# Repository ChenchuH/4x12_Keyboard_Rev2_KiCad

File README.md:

# 4x12_Keyboard_Rev2_KiCad
4x12 Ortholinear Keeb with RP2040

## Bill of Materials

| Reference(s) | Qty | Value | Footprint |
|---|---:|---|---|
| D1–D48 | 48 | 1N4148W | `Diode_SMD:D_SOD-123` |
| ENC1 | 1 | RotaryEncoder | `Rotary_Encoder:RotaryEncoder_Alps_EC12E_Vertical_H20mm` |
| LED1 | 1 | 3V | `LED_SMD:LED_0805_2012Metric_Pad1.15x1.40mm_HandSolder` |
| LED2 | 1 | 2.1 | `LED_SMD:LED_0805_2012Metric_Pad1.15x1.40mm_HandSolder` |
| Q1 | 1 | MMBT3904 | `Package_TO_SOT_SMD:SOT-23` |
| R1 | 1 | 100 | `Resistor_SMD:R_0805_2012Metric` |
| R2 | 1 | 1k | `Resistor_SMD:R_0805_2012Metric` |
| R3 | 1 | 330 | `Resistor_SMD:R_0805_2012Metric` |
| SW1–SW48 | 48 | SW_Push | `Keyboardparts:SW_Cherry_MX_1.00u_PCB_NoSilkScreen` |
| U1 | 1 | XIAO-RP2040-Plus-SMD | `Seeed_XIAO:XIAO-RP2040-Plus-SMD` |

### 5 PCBs cost roughly $60 USD from JLPCB, be sure to get a stencil as well for SMD diodes, 48 will get tedious and difficult even in the 0805 package.

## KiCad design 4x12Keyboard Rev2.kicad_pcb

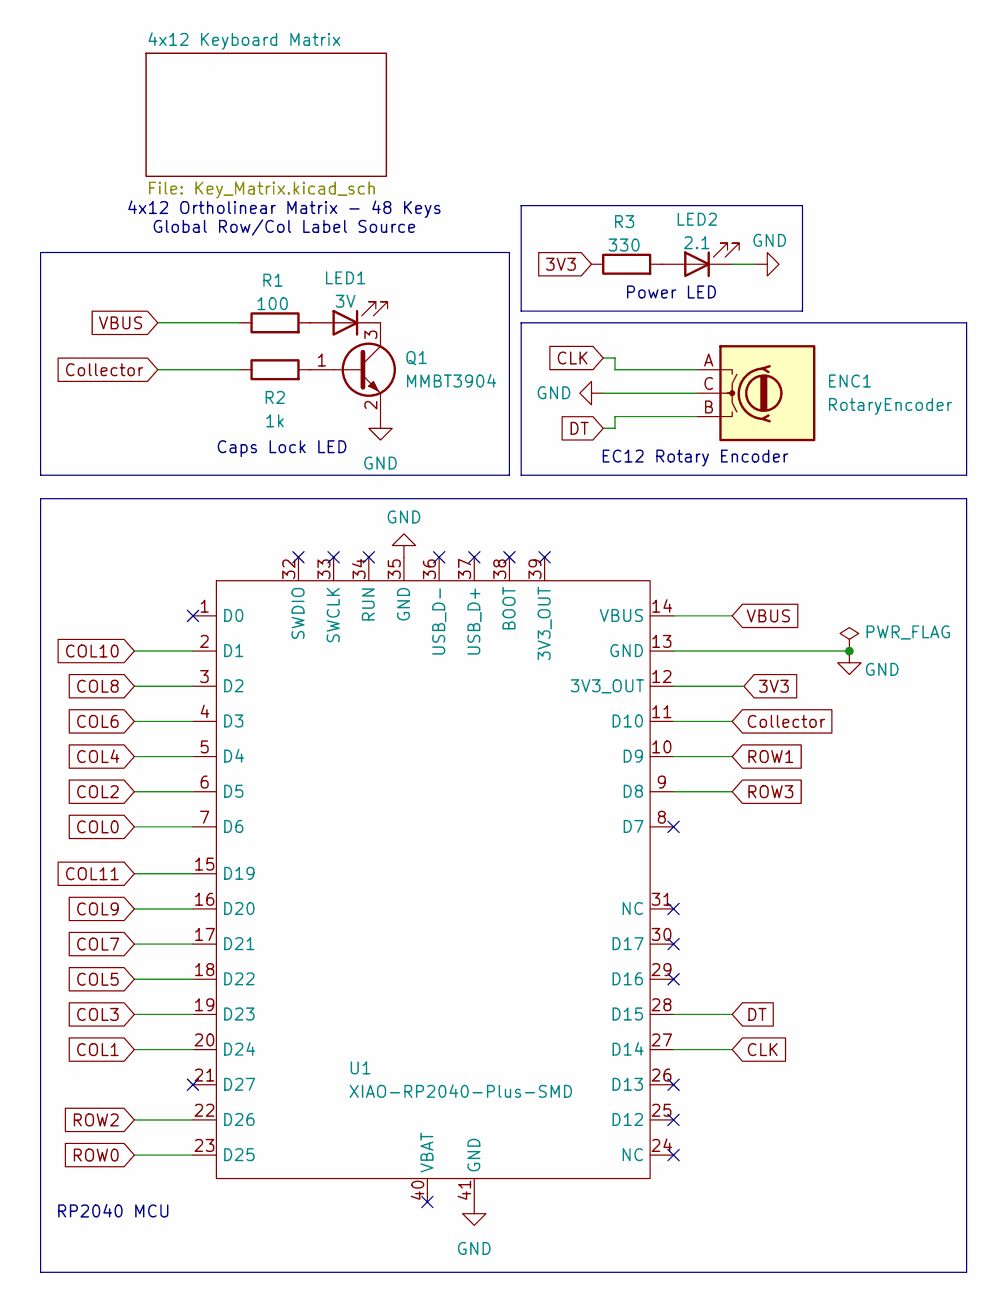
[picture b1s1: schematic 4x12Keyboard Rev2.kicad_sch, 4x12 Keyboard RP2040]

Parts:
ENC1: RotaryEncoder; RotaryEncoder_Alps_EC12E_Vertical_H20mm
LED1: 3V; LED_0805_2012Metric_Pad1.15x1.40mm_HandSolder
LED2: 2.1; LED_0805_2012Metric_Pad1.15x1.40mm_HandSolder
Q1: MMBT3904; SOT-23
R1: 100; R_0805_2012Metric_Pad1.20x1.40mm_HandSolder
R2: 1k; R_0805_2012Metric_Pad1.20x1.40mm_HandSolder
R3: 330; R_0805_2012Metric_Pad1.20x1.40mm_HandSolder
U1: XIAO-RP2040-Plus-SMD

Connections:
3V3: R3.1, U1.12 (3V3_OUT)
CLK: ENC1.A, U1.27 (D14)
COL0: U1.7 (D6); also elsewhere on the board
COL1: U1.20 (D24); also elsewhere on the board
COL2: U1.6 (D5); also elsewhere on the board
COL3: U1.19 (D23); also elsewhere on the board
COL4: U1.5 (D4); also elsewhere on the board
COL5: U1.18 (D22); also elsewhere on the board
COL6: U1.4 (D3); also elsewhere on the board
COL7: U1.17 (D21); also elsewhere on the board
COL8: U1.3 (D2); also elsewhere on the board
COL9: U1.16 (D20); also elsewhere on the board
COL10: U1.2 (D1); also elsewhere on the board
COL11: U1.15 (D19); also elsewhere on the board
Collector: R2.1, U1.11 (D10)
DT: ENC1.B, U1.28 (D15)
GND: ENC1.C, LED2.1 (K), Q1.2 (E), U1.13 (GND), U1.35 (GND), U1.41 (GND)
unnamed: LED1.2 (A), R1.2
unnamed: LED1.1 (K), Q1.3 (C)
unnamed: LED2.2 (A), R3.2
unnamed: Q1.1 (B), R2.2
ROW0: U1.23 (D25); also elsewhere on the board
ROW1: U1.10 (D9); also elsewhere on the board
ROW2: U1.22 (D26); also elsewhere on the board
ROW3: U1.9 (D8); also elsewhere on the board
VBUS: R1.1, U1.14 (VBUS)

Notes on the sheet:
Caps Lock LED
4x12 Ortholinear Matrix - 48 Keys Global Row/Col Label Source
EC12 Rotary Encoder
RP2040 MCU
Power LED

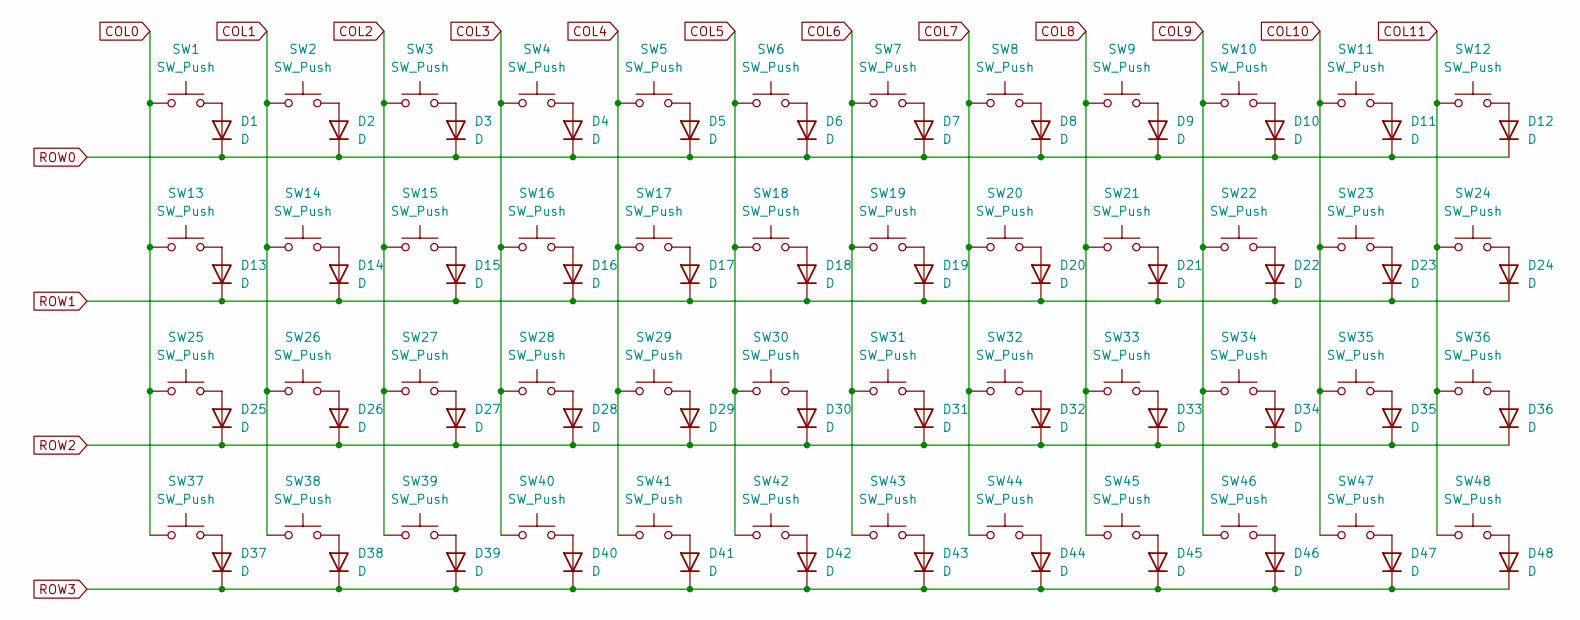
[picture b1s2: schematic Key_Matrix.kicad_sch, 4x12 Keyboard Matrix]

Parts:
D1, D2, D3, D4, D5, D6, D7, D8, D9, D10, D11, D12, D13, D14, D15, D16, D17, D18, D19, D20, D21, D22, D23, D24, D25, D26, D27, D28, D29, D30, D31, D32, D33, D34, D35, D36, D37, D38, D39, D40, D41, D42, D43, D44, D45, D46, D47, D48: D; D_SOD-123
SW1, SW2, SW3, SW4, SW5, SW6, SW7, SW8, SW9, SW10, SW11, SW12, SW13, SW14, SW15, SW16, SW17, SW18, SW19, SW20, SW21, SW22, SW23, SW24, SW25, SW26, SW27, SW28, SW29, SW30, SW31, SW32, SW33, SW34, SW35, SW36, SW37, SW38, SW39, SW40, SW41, SW42, SW43, SW44, SW45, SW46, SW47, SW48: SW_Push; SW_Cherry_MX_1.00u_PCB_NoSilkScreen

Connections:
COL0: SW1.1, SW13.1, SW25.1, SW37.1; also elsewhere on the board
COL1: SW2.1, SW14.1, SW26.1, SW38.1; also elsewhere on the board
COL2: SW3.1, SW15.1, SW27.1, SW39.1; also elsewhere on the board
COL3: SW4.1, SW16.1, SW28.1, SW40.1; also elsewhere on the board
COL4: SW5.1, SW17.1, SW29.1, SW41.1; also elsewhere on the board
COL5: SW6.1, SW18.1, SW30.1, SW42.1; also elsewhere on the board
COL6: SW7.1, SW19.1, SW31.1, SW43.1; also elsewhere on the board
COL7: SW8.1, SW20.1, SW32.1, SW44.1; also elsewhere on the board
COL8: SW9.1, SW21.1, SW33.1, SW45.1; also elsewhere on the board
COL9: SW10.1, SW22.1, SW34.1, SW46.1; also elsewhere on the board
COL10: SW11.1, SW23.1, SW35.1, SW47.1; also elsewhere on the board
COL11: SW12.1, SW24.1, SW36.1, SW48.1; also elsewhere on the board
unnamed: D1.2 (A), SW1.2
unnamed: D2.2 (A), SW2.2
unnamed: D3.2 (A), SW3.2
unnamed: D4.2 (A), SW4.2
unnamed: D5.2 (A), SW5.2
unnamed: D6.2 (A), SW6.2
unnamed: D7.2 (A), SW7.2
unnamed: D8.2 (A), SW8.2
unnamed: D9.2 (A), SW9.2
unnamed: D10.2 (A), SW10.2
unnamed: D11.2 (A), SW11.2
unnamed: D12.2 (A), SW12.2
unnamed: D13.2 (A), SW13.2
unnamed: D14.2 (A), SW14.2
unnamed: D15.2 (A), SW15.2
unnamed: D16.2 (A), SW16.2
unnamed: D17.2 (A), SW17.2
unnamed: D18.2 (A), SW18.2
unnamed: D19.2 (A), SW19.2
unnamed: D20.2 (A), SW20.2
unnamed: D21.2 (A), SW21.2
unnamed: D22.2 (A), SW22.2
unnamed: D23.2 (A), SW23.2
unnamed: D24.2 (A), SW24.2
unnamed: D25.2 (A), SW25.2
unnamed: D26.2 (A), SW26.2
unnamed: D27.2 (A), SW27.2
unnamed: D28.2 (A), SW28.2
unnamed: D29.2 (A), SW29.2
unnamed: D30.2 (A), SW30.2
unnamed: D31.2 (A), SW31.2
unnamed: D32.2 (A), SW32.2
unnamed: D33.2 (A), SW33.2
unnamed: D34.2 (A), SW34.2
unnamed: D35.2 (A), SW35.2
unnamed: D36.2 (A), SW36.2
unnamed: D37.2 (A), SW37.2
unnamed: D38.2 (A), SW38.2
unnamed: D39.2 (A), SW39.2
unnamed: D40.2 (A), SW40.2
unnamed: D41.2 (A), SW41.2
unnamed: D42.2 (A), SW42.2
unnamed: D43.2 (A), SW43.2
unnamed: D44.2 (A), SW44.2
unnamed: D45.2 (A), SW45.2
unnamed: D46.2 (A), SW46.2
unnamed: D47.2 (A), SW47.2
unnamed: D48.2 (A), SW48.2
ROW0: D1.1 (K), D2.1 (K), D3.1 (K), D4.1 (K), D5.1 (K), D6.1 (K), D7.1 (K), D8.1 (K), D9.1 (K), D10.1 (K), D11.1 (K), D12.1 (K); also elsewhere on the board
ROW1: D13.1 (K), D14.1 (K), D15.1 (K), D16.1 (K), D17.1 (K), D18.1 (K), D19.1 (K), D20.1 (K), D21.1 (K), D22.1 (K), D23.1 (K), D24.1 (K); also elsewhere on the board
ROW2: D25.1 (K), D26.1 (K), D27.1 (K), D28.1 (K), D29.1 (K), D30.1 (K), D31.1 (K), D32.1 (K), D33.1 (K), D34.1 (K), D35.1 (K), D36.1 (K); also elsewhere on the board
ROW3: D37.1 (K), D38.1 (K), D39.1 (K), D40.1 (K), D41.1 (K), D42.1 (K), D43.1 (K), D44.1 (K), D45.1 (K), D46.1 (K), D47.1 (K), D48.1 (K); also elsewhere on the board

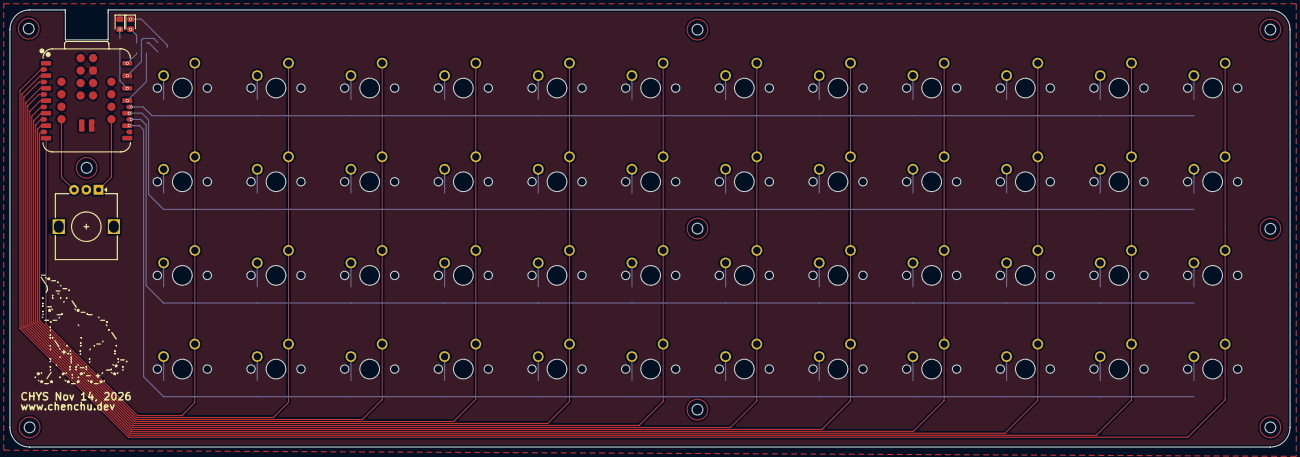
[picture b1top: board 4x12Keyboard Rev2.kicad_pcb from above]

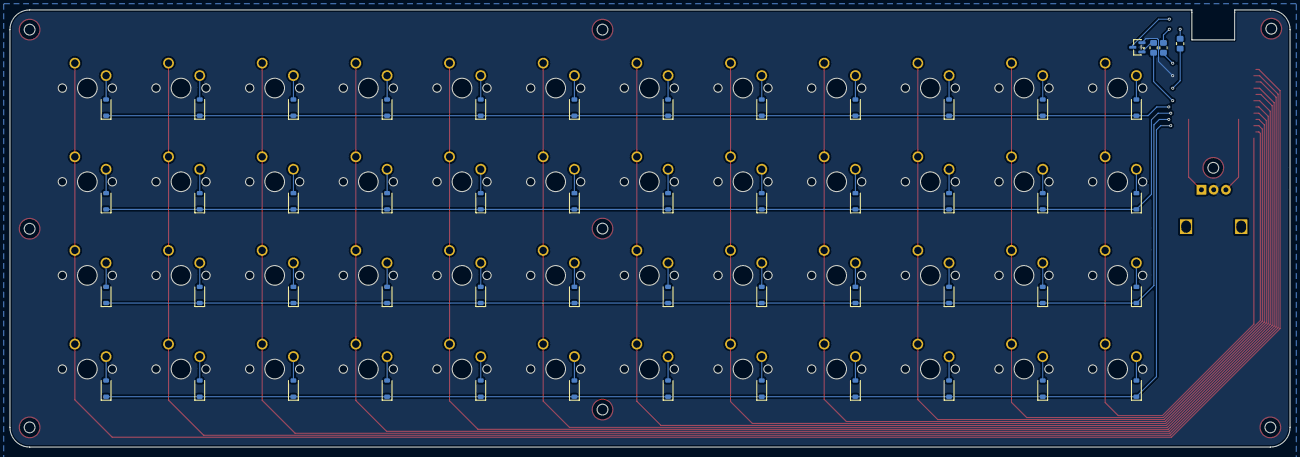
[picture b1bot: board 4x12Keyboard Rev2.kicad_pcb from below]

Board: 2 copper layers, 260.3 x 88.9 mm, 104 parts (52 on the bottom side), 74 nets.
